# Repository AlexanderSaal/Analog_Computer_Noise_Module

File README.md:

# Analog_Computer_Noise_Module
A frequency selectable Noise Module in a rack format for analog computing.

## Module Schematic

The noise is taken from a Zener diode, then slightly amplified and DC shifted to be feed into a low pass filter. The cutoff frequency can be selected with a rotary switch, which operates an adjustable oscillator. The signal is DC offset corrected after the filter and then amplified.

<ins> Noise: </ins>\

This module is largely based on [Bernd Ulmanns design and his archive in the Analogmuseum](https://analogmuseum.org/english/homebrew/noise_filter/) (last visited Dec. 2024). It even has the same frequency steps of: 1, 5, 10, 50, 100, 500 and 1000 $Hz$.

The Noise source is based on a Zener diode, following an article of [Steve Hageman on EDN, with the title: White noise source flat from 1Hz to 100kHz](https://www.edn.com/white-noise-source-flat-from-1hz-to-100khz/) (last visited Dec. 2024).

## Issues

The linear power regulator NCP718xSN500 (U1) overheats within seconds. Although it can handle the current, I did not account for the dissipated power. For a $12\,V$ input, the power dissipation is approximately $0.5\,W$, which immediately triggers a thermal shutdown. This failure cascades through the system, shutting down all components on the $+5V$ rail. 

More problematic is the ripple introduced around the diode used as the noise source. It causes slight variations in the single-digit $mV$ range, which pass through the high-pass filter and amplifier, leading to a significant offset voltage after the first stage. The voltage measured at test point $TP2$ is already outside of specifications.

For now, the recommended solution is to either cool or replace the linear power regulator.

## List of special Components:

- frequency filter :[MAX7407](https://www.digikey.de/en/products/detail/analog-devices-inc-maxim-integrated/MAX7407ESA/1513411)
- oscillator: [LTC6900](https://www.digikey.de/en/products/detail/analog-devices-inc/LTC6900CS5-TRMPBF/1115937)
- Rotary switch, 12 pole, 2 layers: [SWITCH ROTARY 2-12POS](https://www.digikey.de/en/products/detail/grayhill-inc/71BD30-02-1-AJN/98669)

## Bill of materials:

<ins> Main Noise Module: </ins>
|                                             |                     |           |          | 
|---------------------------------------------|---------------------|-----------|----------|
| References                                  | Value               | Footprint | Quantity | 
| C6, C7, C8, C9, C11, C12                    | 100n                | 1206/3216Metric | 6        | 
| C3, C4, C5                                  | 1u                  | 1206/3216Metric | 3        | 
| C1, C2                                      | 10u                 | 1206/3216Metric | 2        | 
| C10                                         | 2n                  | 1206/3216Metric | 1        | 
| R3, R4, R6, R7, R9, R10, R12, R13, R14, R18 | 100k                | 1206/3216Metric | 10       | 
| R1, R2                                      | 5k6                 | 1206/3216Metric | 2        | 
| R5                                          | 1M                  | 1206/3216Metric | 1        | 
| R8                                          | 2M                  | 1206/3216Metric | 1        | 
| R11                                         | 10k                 | 1206/3216Metric | 1        | 
| R15                                         | 24k                 | 1206/3216Metric | 1        | 
| R16                                         | 1.2M                | 1206/3216Metric | 1        | 
| R17                                         | 200k                | 1206/3216Metric | 1        | 
| D1                                          | GREEN Diode         | 1206/3216Metric | 1        | 
| D2                                          | RED Diode           | 1206/3216Metric | 1        | 
| D5                                          | Zener Diode         | any             | 1        | 
| U2, U3                                      | VCAN16A2-03S-E3-08  | SOT23-3         | 2        | 
| U1                                          | NCP718xSN500        | SOT-23-5        | 1        | 
| U4                                          | TL074               | SOIC-14         | 1        | 
| U5                                          | LTC6900             | TSOT-23-5       | 1        | 
| U6                                          | 74HC393             | SOIC-14         | 1        | 
| U7                                          | MAX740X             | SOIC-8          | 1        | 
| RV1, RV2, RV4, RV5, RV6, RV7, RV8           | 100k                | Potentiometer_Bourns_3296W_Vertical | 7        | 
| Q1                                          | PMV250EPEA          | SOT-23          | 1        | 
| Q2                                          | PMV450ENEA          | SOT-23          | 1        | 
| J1                                          | Conn_01x11_Pin      | | 1        | 
| J3                                          | Conn_02x05_Odd_Even | | 1        | 

<ins> Middleplate: </ins>
|              |                        |           |          | 
|--------------|------------------------|-----------|----------| 
| References   | Value                  | Footprint | Quantity | 
| Poti1, Poti2 | 100k Potentiometer     |           | 1        |
|              | SP12T switch, 2 layers |           | 1        |
|              | 2mm banana plug socket |           | 1        |

## License

This work is published under the [CERN Open Hardware Licence Version 2 - Strongly Reciprocal](LICENSE)

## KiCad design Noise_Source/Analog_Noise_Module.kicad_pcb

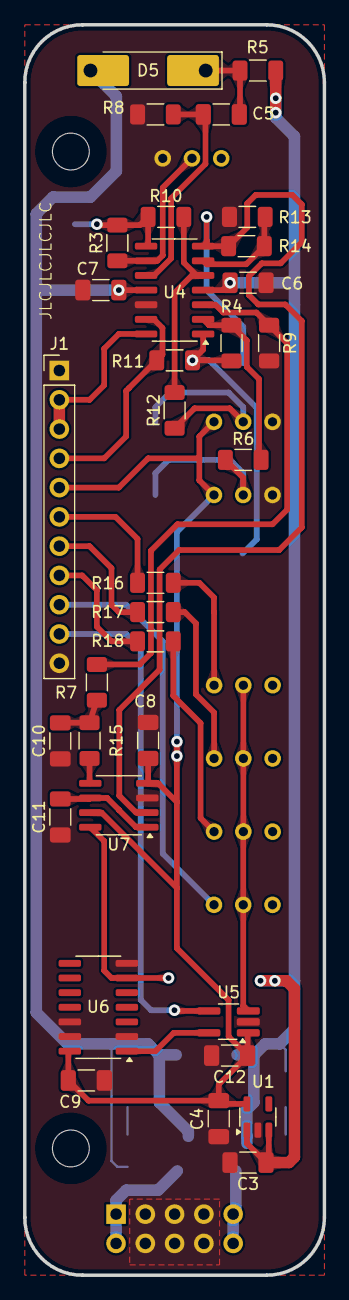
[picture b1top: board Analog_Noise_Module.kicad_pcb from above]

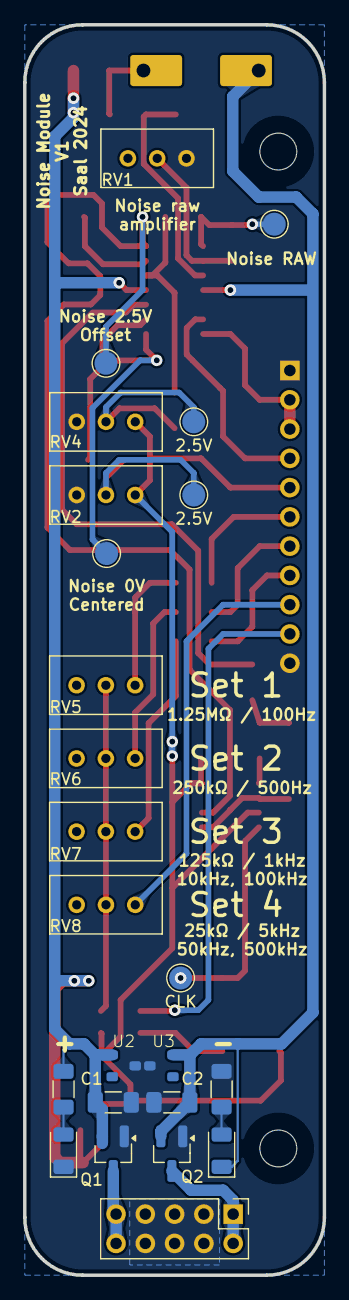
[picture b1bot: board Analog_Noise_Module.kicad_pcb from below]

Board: 2 copper layers, 26.0 x 108.5 mm, 59 parts (24 on the bottom side), 36 nets.

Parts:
C1, C2: 10u; C_1206_3216Metric_Pad1.33x1.80mm_HandSolder
C3, C4, C5: 1u; C_1206_3216Metric_Pad1.33x1.80mm_HandSolder
C6, C7, C8, C9, C11, C12: 100n; C_1206_3216Metric_Pad1.33x1.80mm_HandSolder
C10: 2n; C_1206_3216Metric_Pad1.33x1.80mm_HandSolder
D1: 12V_GREEN; LED_1206_3216Metric
D2: -12V_RED; LED_1206_3216Metric
D5: D_Zener_Small; D_MELF-RM10_Universal_Handsoldering
H1, H2: MountingHole; MountingHole_3.2mm_M3_DIN965
J1: Conn_01x11_Pin; PinHeader_1x11_P2.54mm_Vertical
J3: Conn_02x05_Odd_Even; PinHeader_2x05_P2.54mm_Vertical
Q1: PMV250EPEA; SOT-23_Handsoldering
Q2: PMV450ENEA; SOT-23_Handsoldering
R1, R2: 5k6; R_1206_3216Metric_Pad1.30x1.75mm_HandSolder
R3, R4, R6, R7, R9, R10, R12, R13, R14, R18: 100k; R_1206_3216Metric_Pad1.30x1.75mm_HandSolder
R5: 1M; R_1206_3216Metric_Pad1.30x1.75mm_HandSolder
R8: 2M; R_1206_3216Metric_Pad1.30x1.75mm_HandSolder
R11: 10k; R_1206_3216Metric_Pad1.30x1.75mm_HandSolder
R15: 24k; R_1206_3216Metric_Pad1.30x1.75mm_HandSolder
R16: 1.2M; R_1206_3216Metric_Pad1.30x1.75mm_HandSolder
R17: 200k; R_1206_3216Metric_Pad1.30x1.75mm_HandSolder
RV1, RV2, RV4, RV5, RV6, RV7, RV8: 100k; Potentiometer_Bourns_3296W_Vertical
TP1, TP4: 2.5V; TestPoint_Pad_D2.0mm
TP2: RAW; TestPoint_Pad_D2.0mm
TP3: NOISE_0V_centered; TestPoint_Pad_D2.0mm
TP5: NOISE_2.5V_Offset; TestPoint_Pad_D2.0mm
TP6: CLK; TestPoint_Pad_D2.0mm
U1: NCP718xSN500; SOT-23-5
U2, U3: VCAN16A2-03S-E3-08
U4: TL074; SOIC-14_3.9x8.7mm_P1.27mm
U5: TSOT-23-5_HandSoldering
U6: 74HC393; SOIC-14_3.9x8.7mm_P1.27mm
U7: MAX740X; SOIC-8_3.9x4.9mm_P1.27mm

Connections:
+12V: C1.1, C3.1, C6.1, Q1.2 (S), R1.1, R5.1, U1.1 (IN), U1.3 (EN), U2.1 (IN1), U4.4 (V+)
+12V_IN: J3.9, J3.10, Q1.3 (D)
-12V: C2.1, C7.2, D2.1 (K), D5.2 (A), Q2.2 (S), U3.2 (IN2), U4.11 (V-)
-12V_IN: J3.1, J3.2, Q2.3 (D)
CLK: TP6.1, U6.6 (Q3_1), U7.8 (CLK)
DIV: J1.10, U5.4 (DIV)
GND: C1.2, C2.2, C3.2, C4.2, C6.2, C7.1, C8.2, C9.2, C10.1, C11.1, C12.2, D1.1 (K), J1.1, J1.11, J3.3, J3.4, J3.5, J3.6, J3.7, J3.8, Q1.1 (G), Q2.1 (G), R2.1, R8.2, R9.2, R13.1, RV1.3, RV2.3, RV4.3, U1.2 (GND), U2.3 (OUT), U3.3 (OUT), U4.12 (+), U5.2 (GND), U6.2 (MR_1), U6.7 (GND), U6.12 (MR_2), U6.13 (\CLK_2), U7.3 (GND)
MCLK: U5.5 (OUT), U6.1 (\CLK_1)
unnamed: D1.2 (A), R1.2
unnamed: D2.2 (A), R2.2
unnamed: C5.2, D5.1 (K), R5.2
unnamed: R6.1, RV2.2, TP1.1
unnamed: R12.1, RV4.2, TP4.1
unnamed: R16.2, RV5.3
unnamed: R17.2, RV6.3
unnamed: R18.2, RV7.3
unnamed: R7.2, R9.1, U4.3 (+)
unnamed: R4.1, R6.2, U4.2 (-)
unnamed: R10.2, R12.2, U4.5 (+)
unnamed: R13.2, R14.1, U4.6 (-)
unnamed: C5.1, R8.1, U4.10 (+)
unnamed: R3.1, RV1.2, U4.9 (-)
unnamed: C11.2, U7.1 (COM), U7.6 (Offset)
unnamed: R15.1, U7.5 (OUT)
Noise: R3.2, R10.1, TP2.1, U4.8
Noise_IN: R14.2, TP5.1, U4.7, U7.2 (IN)
Noise_OUT: J1.2, J1.3, U4.14
Noise_centered: R4.2, R11.1, TP3.1, U4.1
Noise_filtered: C10.2, R7.1, R15.2
Poti1: J1.4, R11.2, U4.13 (-)
SET: RV5.2, RV6.2, RV7.2, RV8.2, U5.3 (SET)
SET_1: J1.6, R16.1
SET_2: J1.7, R17.1
SET_3: J1.8, R18.1
SET_4: J1.9, RV8.3
VCC: C4.1, C8.1, C9.1, C12.1, J1.5, RV2.1, RV4.1, U1.5 (OUT), U5.1 (VCC), U6.14 (VCC), U7.4 (VDD), U7.7 (\SHDN)

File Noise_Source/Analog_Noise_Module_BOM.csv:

"Reference","Value","Footprint","QUANTITY"
"C1,C2","10u","Capacitor_SMD:C_1206_3216Metric_Pad1.33x1.80mm_HandSolder","2"
"C3-C5","1u","Capacitor_SMD:C_1206_3216Metric_Pad1.33x1.80mm_HandSolder","3"
"C6-C9,C11,C12","100n","Capacitor_SMD:C_1206_3216Metric_Pad1.33x1.80mm_HandSolder","6"
"C10","2n","Capacitor_SMD:C_1206_3216Metric_Pad1.33x1.80mm_HandSolder","1"
"D1","12V_GREEN","LED_SMD:LED_1206_3216Metric","1"
"D2","-12V_RED","LED_SMD:LED_1206_3216Metric","1"
"D5","D_Zener_Small","Diode_SMD:D_MELF-RM10_Universal_Handsoldering","1"
"J1","Conn_01x11_Pin","Connector_PinHeader_2.54mm:PinHeader_1x11_P2.54mm_Vertical","1"
"J3","Conn_02x05_Odd_Even","Connector_PinHeader_2.54mm:PinHeader_2x05_P2.54mm_Vertical","1"
"Q1","PMV250EPEA","Package_TO_SOT_SMD:SOT-23_Handsoldering","1"
"Q2","PMV450ENEA","Package_TO_SOT_SMD:SOT-23_Handsoldering","1"
"R1,R2","5k6","Resistor_SMD:R_1206_3216Metric_Pad1.30x1.75mm_HandSolder","2"
"R3,R4,R6,R7,R9,R10,R12-R14,R18","100k","Resistor_SMD:R_1206_3216Metric_Pad1.30x1.75mm_HandSolder","10"
"R5","1M","Resistor_SMD:R_1206_3216Metric_Pad1.30x1.75mm_HandSolder","1"
"R8","2M","Resistor_SMD:R_1206_3216Metric_Pad1.30x1.75mm_HandSolder","1"
"R11","10k","Resistor_SMD:R_1206_3216Metric_Pad1.30x1.75mm_HandSolder","1"
"R15","24k","Resistor_SMD:R_1206_3216Metric_Pad1.30x1.75mm_HandSolder","1"
"R16","1.2M","Resistor_SMD:R_1206_3216Metric_Pad1.30x1.75mm_HandSolder","1"
"R17","200k","Resistor_SMD:R_1206_3216Metric_Pad1.30x1.75mm_HandSolder","1"
"RV1,RV2,RV4-RV8","100k","Potentiometer_THT:Potentiometer_Bourns_3296W_Vertical","7"
"TP1,TP4","2.5V","TestPoint:TestPoint_Pad_D2.0mm","2"
"TP2","RAW","TestPoint:TestPoint_Pad_D2.0mm","1"
"TP3","NOISE_0V_centered","TestPoint:TestPoint_Pad_D2.0mm","1"
"TP5","NOISE_2.5V_Offset","TestPoint:TestPoint_Pad_D2.0mm","1"
"TP6","CLK","TestPoint:TestPoint_Pad_D2.0mm","1"
"U1","NCP718xSN500","Package_TO_SOT_SMD:SOT-23-5","1"
"U2,U3","VCAN16A2","analog_computing:VCAN16A2-03S-E3-08","2"
"U4","TL074","Package_SO:SOIC-14_3.9x8.7mm_P1.27mm","1"
"U5","LTC6900CS5","Package_TO_SOT_SMD:TSOT-23-5_HandSoldering","1"
"U6","74HC393","Package_SO:SOIC-14_3.9x8.7mm_P1.27mm","1"
"U7","MAX740X","Package_SO:SOIC-8_3.9x4.9mm_P1.27mm","1"

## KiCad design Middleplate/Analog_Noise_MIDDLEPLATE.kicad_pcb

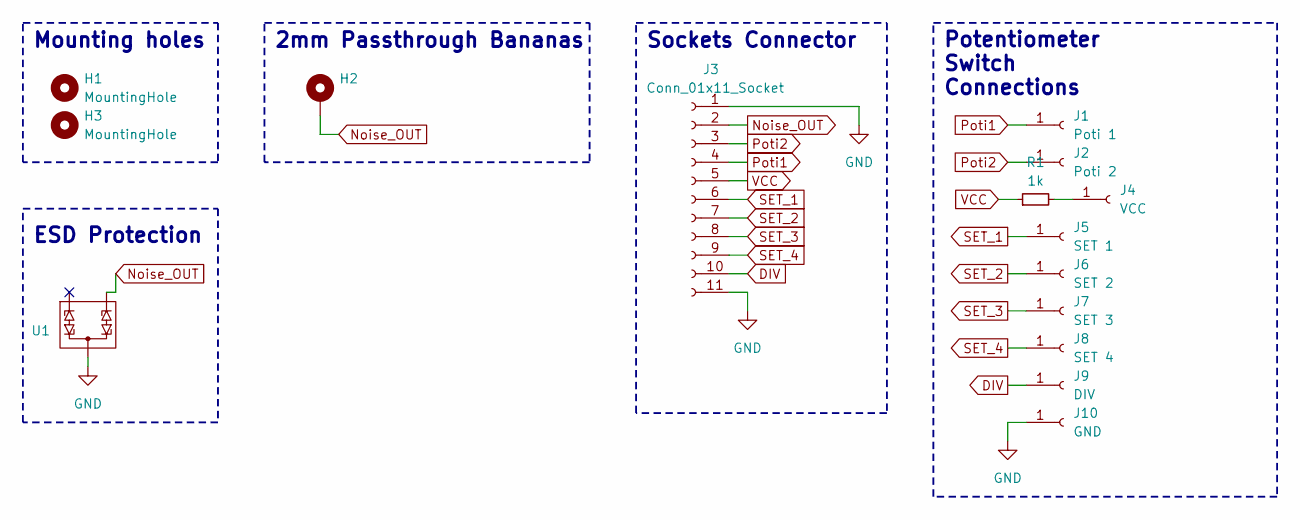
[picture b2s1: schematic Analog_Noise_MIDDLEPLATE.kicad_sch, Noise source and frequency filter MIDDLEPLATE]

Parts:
H1, H3: MountingHole; MountingHole_3.2mm_M3_DIN965
H2: MountingHole_Pad; MountingHole_4.3mm_M4_DIN965_Pad
J1: Poti 1; SolderWire-0.75sqmm_1x01_D1.25mm_OD3.5mm
J2: Poti 2; SolderWire-0.75sqmm_1x01_D1.25mm_OD3.5mm
J3: Conn_01x11_Socket; PinSocket_1x11_P2.54mm_Vertical
J4: VCC; SolderWire-0.75sqmm_1x01_D1.25mm_OD3.5mm
J5: SET 1; SolderWire-0.75sqmm_1x01_D1.25mm_OD3.5mm
J6: SET 2; SolderWire-0.75sqmm_1x01_D1.25mm_OD3.5mm
J7: SET 3; SolderWire-0.75sqmm_1x01_D1.25mm_OD3.5mm
J8: SET 4; SolderWire-0.75sqmm_1x01_D1.25mm_OD3.5mm
J9: DIV; SolderWire-0.75sqmm_1x01_D1.25mm_OD3.5mm
J10: GND; SolderWire-0.75sqmm_1x01_D1.25mm_OD3.5mm
R1: 1k; R_1206_3216Metric_Pad1.30x1.75mm_HandSolder
U1: VCAN16A2-03S-E3-08

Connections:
DIV: J3.10, J9.1
GND: J3.1, J3.11, J10.1, U1.3 (OUT)
unnamed: J4.1, R1.2
Noise_OUT: H2.1, J3.2, U1.2 (IN2)
Poti1: J1.1, J3.4
Poti2: J2.1, J3.3
SET_1: J3.6, J5.1
SET_2: J3.7, J6.1
SET_3: J3.8, J7.1
SET_4: J3.9, J8.1
VCC: J3.5, R1.1

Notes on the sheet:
Sockets Connector
2mm Passthrough Bananas
Potentiometer Switch Connections
ESD Protection
Mounting holes

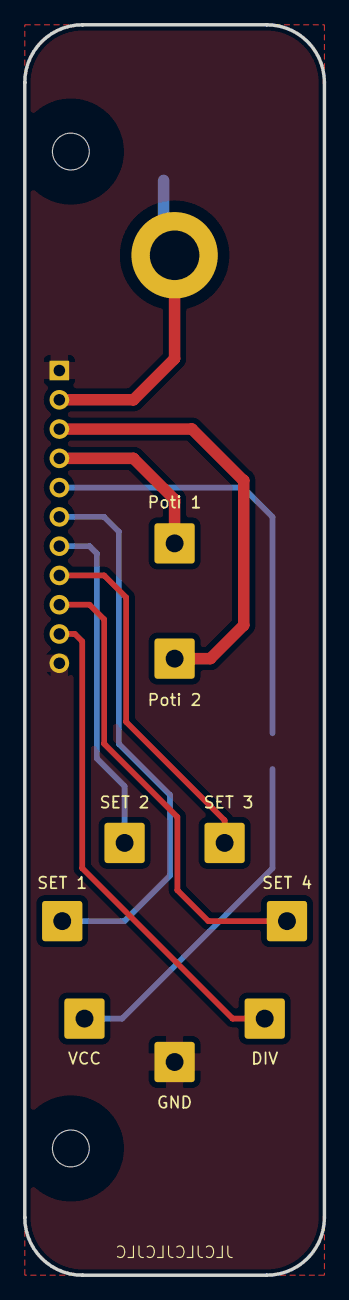
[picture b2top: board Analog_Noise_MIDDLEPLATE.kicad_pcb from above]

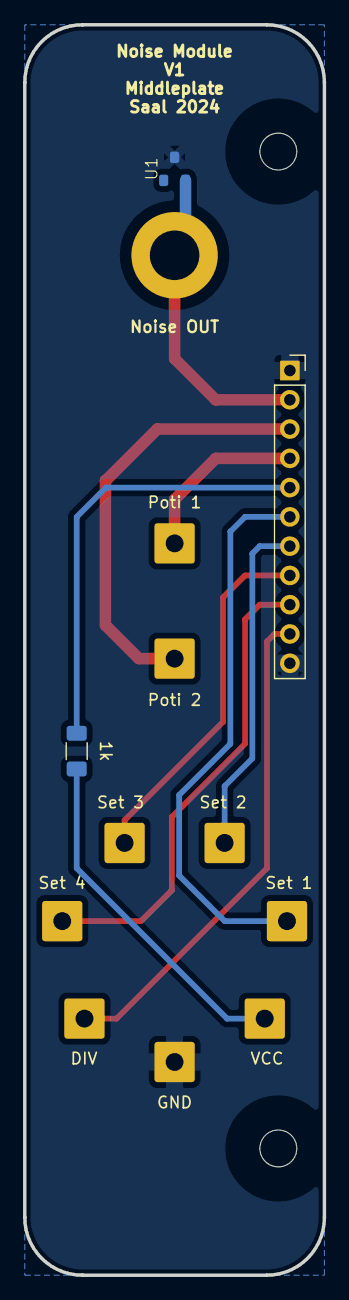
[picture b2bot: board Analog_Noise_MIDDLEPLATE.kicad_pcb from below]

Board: 2 copper layers, 26.0 x 108.5 mm, 15 parts (3 on the bottom side), 11 nets.

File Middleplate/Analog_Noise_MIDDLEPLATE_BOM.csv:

"Reference","Value","Footprint","QUANTITY"
"J1","Poti 1","Connector_Wire:SolderWire-0.75sqmm_1x01_D1.25mm_OD3.5mm","1"
"J2","Poti 2","Connector_Wire:SolderWire-0.75sqmm_1x01_D1.25mm_OD3.5mm","1"
"J3","Conn_01x11_Socket","Connector_PinSocket_2.54mm:PinSocket_1x11_P2.54mm_Vertical","1"
"J4","VCC","Connector_Wire:SolderWire-0.75sqmm_1x01_D1.25mm_OD3.5mm","1"
"J5","SET 1","Connector_Wire:SolderWire-0.75sqmm_1x01_D1.25mm_OD3.5mm","1"
"J6","SET 2","Connector_Wire:SolderWire-0.75sqmm_1x01_D1.25mm_OD3.5mm","1"
"J7","SET 3","Connector_Wire:SolderWire-0.75sqmm_1x01_D1.25mm_OD3.5mm","1"
"J8","SET 4","Connector_Wire:SolderWire-0.75sqmm_1x01_D1.25mm_OD3.5mm","1"
"J9","DIV","Connector_Wire:SolderWire-0.75sqmm_1x01_D1.25mm_OD3.5mm","1"
"J10","GND","Connector_Wire:SolderWire-0.75sqmm_1x01_D1.25mm_OD3.5mm","1"
"R1","1k","Resistor_SMD:R_1206_3216Metric_Pad1.30x1.75mm_HandSolder","1"
"U1","VCAN16A2-03S-E3-08","analog_computing:VCAN16A2-03S-E3-08","1"

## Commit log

2025-02-14 V1 finished and Issues updated
